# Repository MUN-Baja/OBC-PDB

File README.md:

# OBC-PDB
PCB design of Power Distribution Board and the On Board Computer with a ATMEGA2560 uC.

<ul>
  <li> Add 0 Ohm resistor dividers at all A-in to allow for configure voltage dividers
</ul>

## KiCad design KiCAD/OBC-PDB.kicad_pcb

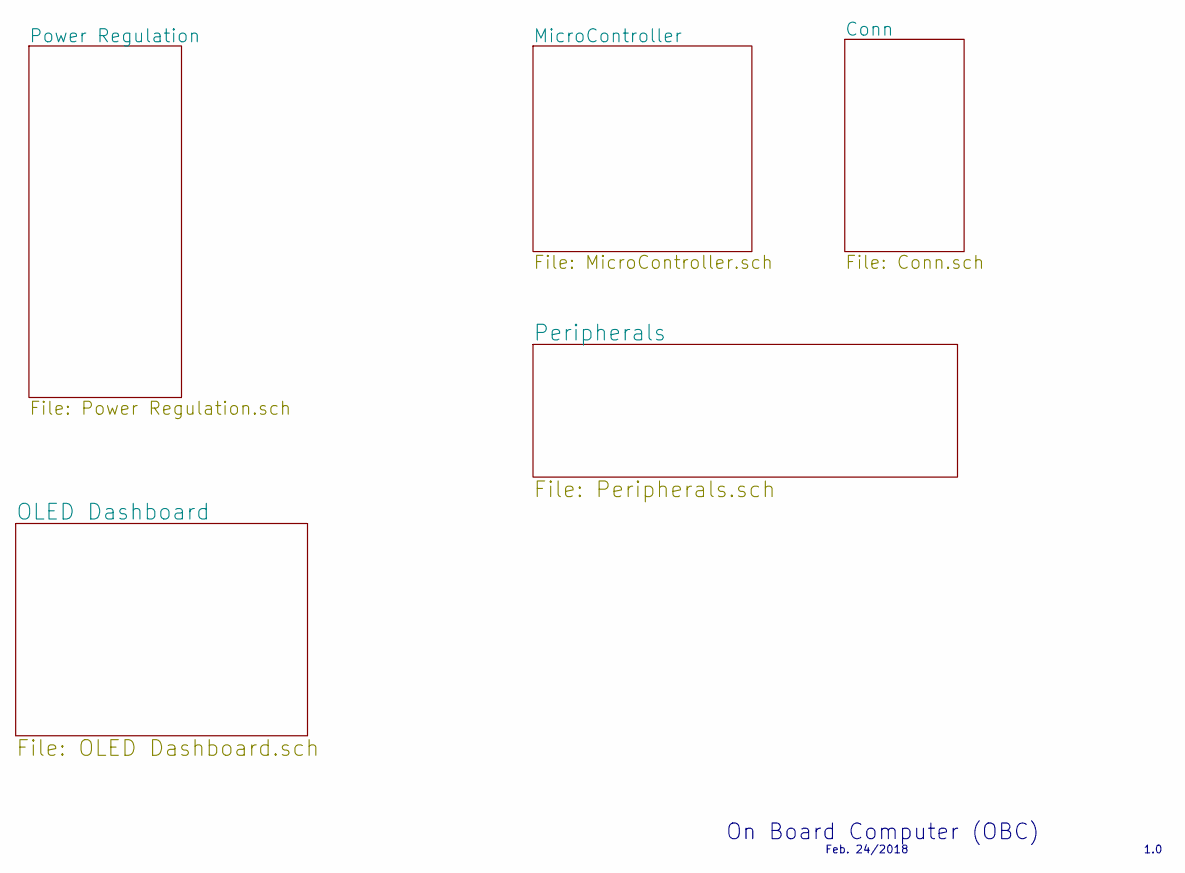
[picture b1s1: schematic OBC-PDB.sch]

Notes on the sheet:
Feb. 24/2018
On Board Computer (OBC)
1.0

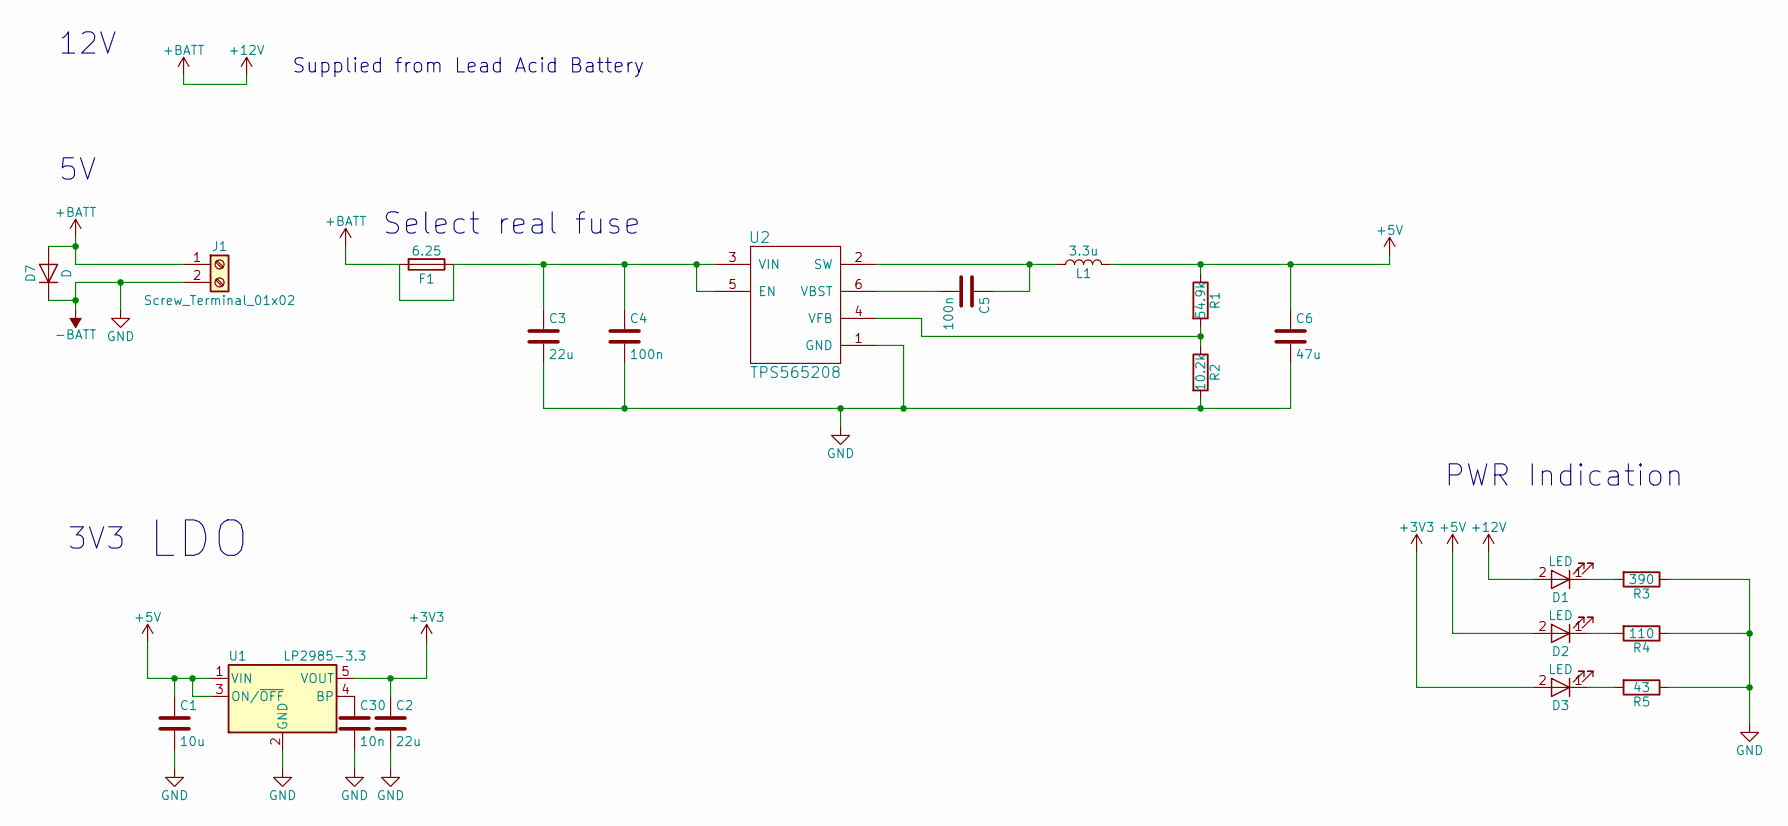
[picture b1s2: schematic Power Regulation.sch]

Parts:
C1: 10u; C_0805
C2: 22u; C_0805
C3: 22u; C_1210
C4, C5: 100n; C_0603
C6: 47u; C_1206
C30: 10n; C_0805
D1, D2, D3: LED; LED_0805
D7: D; R_Axial_DIN0204_L3.6mm_D1.6mm_P5.08mm_Horizontal
F1: 6.25
J1: Screw_Terminal_01x02; TerminalBlock_bornier-2_P5.08mm
L1: 3.3u; XAL7030
R1: 54.9k; R_0402; Tolerance 1%
R2: 10.2k; R_0402; Tolerance 1%
R3: 390; R_0805
R4: 110; R_0805
R5: 43; R_0805
U1: LP2985-3.3; SOT-23-5
U2: TPS565208; TSOT-23-6

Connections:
+3V3: C2.1, D3.2 (A), U1.5 (VOUT); also elsewhere on the board
+5V: C1.1, C6.1, D2.2 (A), L1.2, R1.1, U1.1 (VIN), U1.3 (ON/~OFF~); also elsewhere on the board
+12V: C3.1, C4.1, D1.2 (A), D7.2 (A), F1.1, F1.2, J1.1, U2.3 (VIN), U2.5 (EN); also elsewhere on the board
-BATT: C1.2, C2.2, C3.2, C4.2, C6.2, C30.2, D7.1 (K), J1.2, R2.2, R3.1, R4.1, R5.1, U1.2 (GND), U2.1 (GND); also elsewhere on the board
unnamed: C5.1, L1.1, U2.2 (SW)
unnamed: C5.2, U2.6 (VBST)
unnamed: C30.1, U1.4 (BP)
unnamed: D1.1 (K), R3.2
unnamed: D2.1 (K), R4.2
unnamed: D3.1 (K), R5.2
unnamed: R1.2, R2.1, U2.4 (VFB)

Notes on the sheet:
LDO
Select real fuse
PWR Indication
12V
Supplied from Lead Acid Battery
3V3

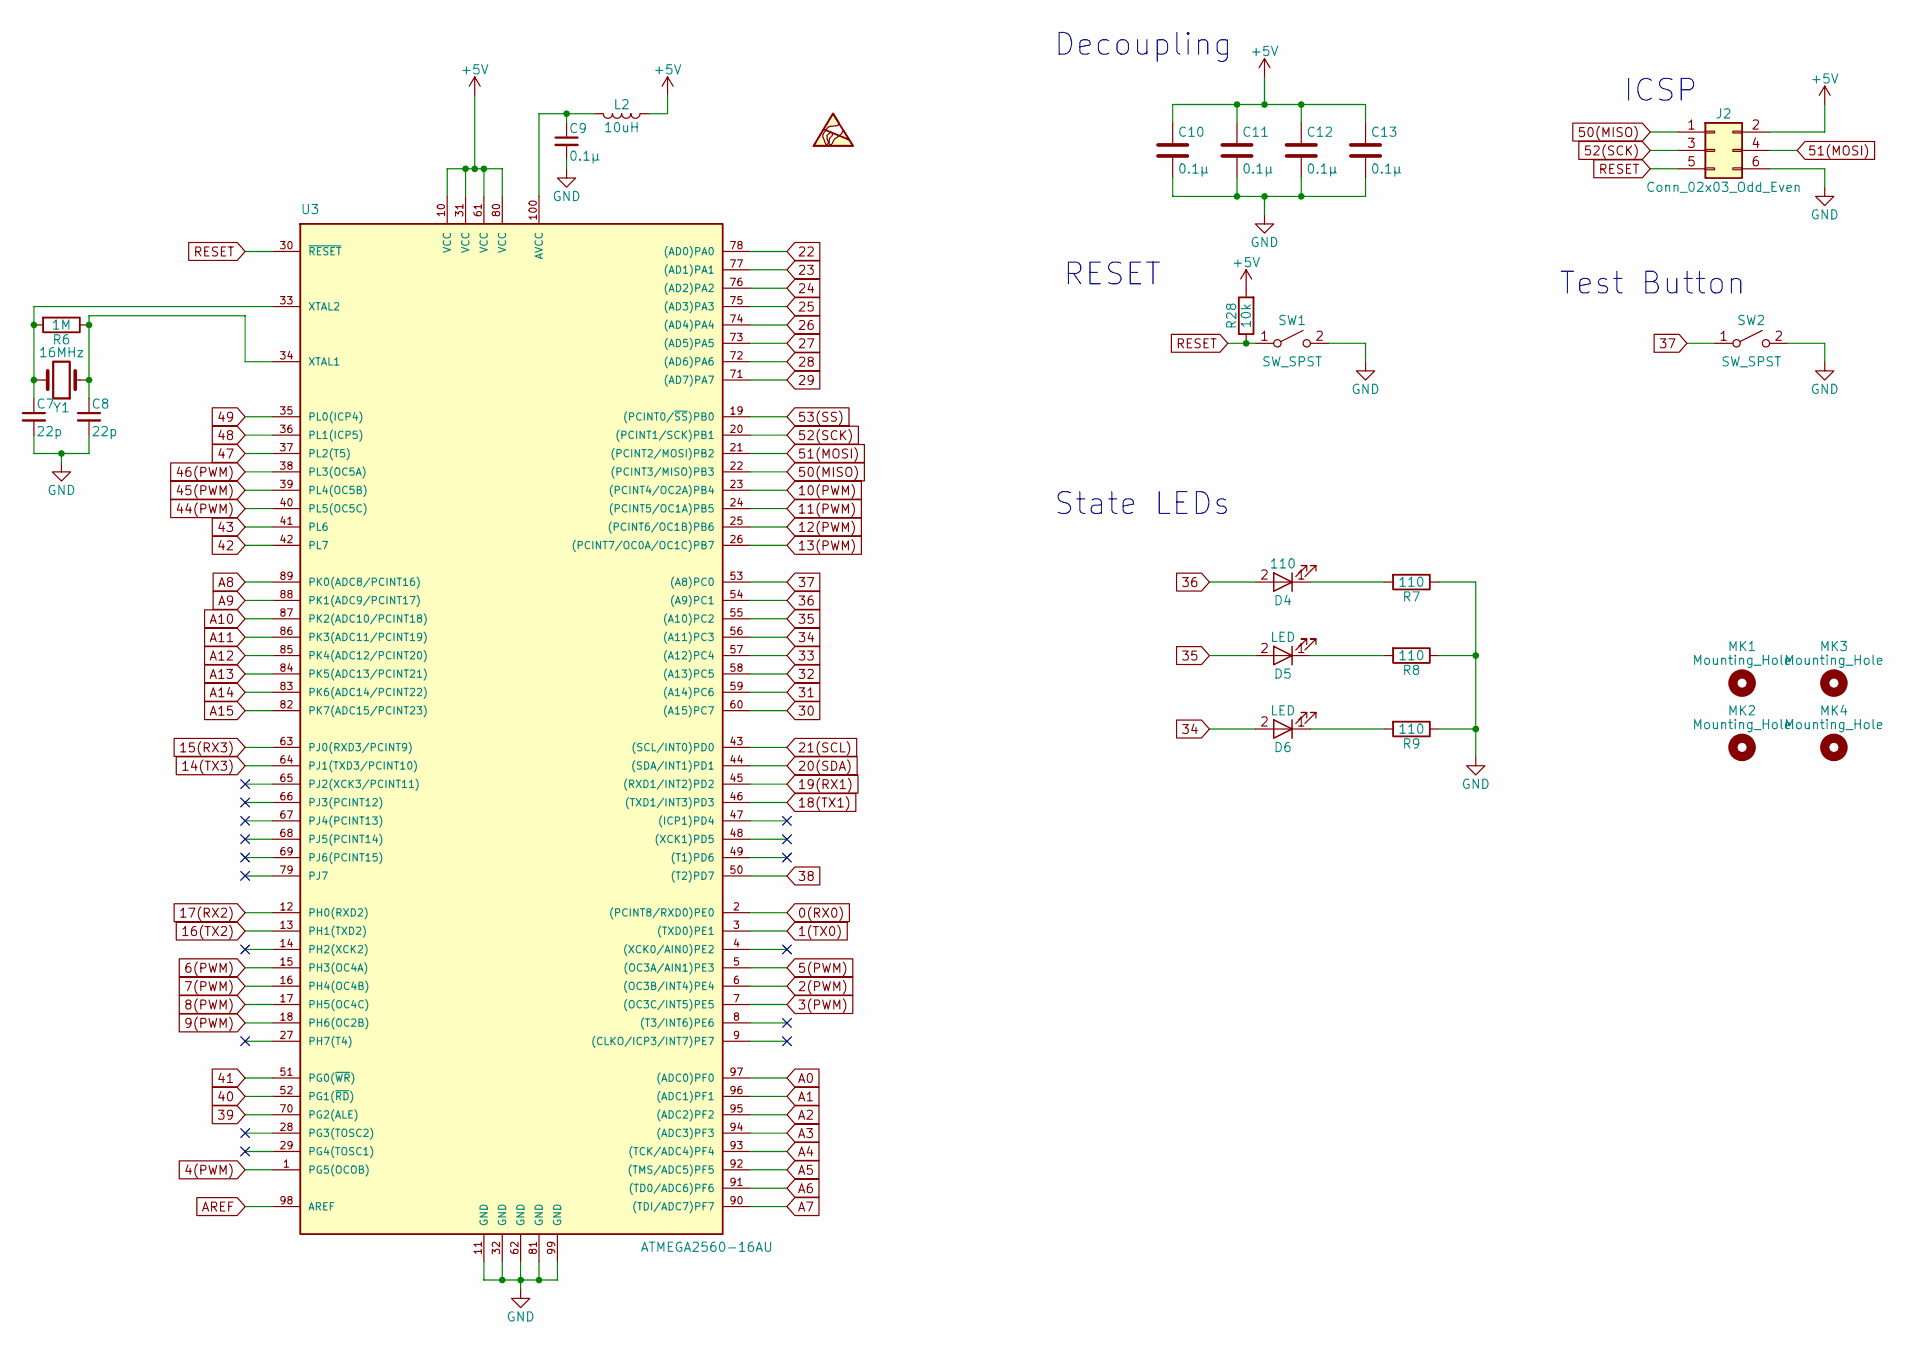
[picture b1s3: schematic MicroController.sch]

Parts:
C7, C8: 22p; C_0805
C9, C10, C11, C12, C13: 0.1µ; C_0805
D4: 110; LED_0805
D5, D6: LED; LED_0805
J2: Conn_02x03_Odd_Even; Pin_Header_Straight_2x03_Pitch2.54mm
L2: 10uH; L-1008
MK1, MK2, MK3, MK4: Mounting_Hole; MountingHole_3.2mm_M3
R6: 1M; R_0805
R7, R8, R9: 110; R_0805
R28: 10k; R_0805
SW1, SW2: SW_SPST; SW_SPST_B3U-1000P
U3: ATMEGA2560-16AU; TQFP-100_14x14mm_Pitch0.5mm
Y1: 16MHz; Crystal_HC49-U_Vertical

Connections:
5(PWM): U3.5 ((OC3A/AIN1)PE3); also elsewhere on the board
6(PWM): U3.15 (PH3(OC4A)); also elsewhere on the board
7(PWM): U3.16 (PH4(OC4B))
8(PWM): U3.17 (PH5(OC4C))
9(PWM): U3.18 (PH6(OC2B))
10(PWM): U3.23 ((PCINT4/OC2A)PB4)
11(PWM): U3.24 ((PCINT5/OC1A)PB5)
12(PWM): U3.25 ((PCINT6/OC1B)PB6); also elsewhere on the board
13(PWM): U3.26 ((PCINT7/OC0A/OC1C)PB7); also elsewhere on the board
14(TX3): U3.64 (PJ1(TXD3/PCINT10))
15(RX3): U3.63 (PJ0(RXD3/PCINT9))
16(TX2): U3.13 (PH1(TXD2)); also elsewhere on the board
17(RX2): U3.12 (PH0(RXD2)); also elsewhere on the board
18(TX1): U3.46 ((TXD1/INT3)PD3)
19(RX1): U3.45 ((RXD1/INT2)PD2)
20(SDA): U3.44 ((SDA/INT1)PD1); also elsewhere on the board
21(SCL): U3.43 ((SCL/INT0)PD0); also elsewhere on the board
22: U3.78 ((AD0)PA0); also elsewhere on the board
23: U3.77 ((AD1)PA1); also elsewhere on the board
24: U3.76 ((AD2)PA2); also elsewhere on the board
25: U3.75 ((AD3)PA3); also elsewhere on the board
26: U3.74 ((AD4)PA4); also elsewhere on the board
27: U3.73 ((AD5)PA5); also elsewhere on the board
28: U3.72 ((AD6)PA6); also elsewhere on the board
29: U3.71 ((AD7)PA7); also elsewhere on the board
30: U3.60 ((A15)PC7)
31: U3.59 ((A14)PC6); also elsewhere on the board
32: U3.58 ((A13)PC5); also elsewhere on the board
33: U3.57 ((A12)PC4); also elsewhere on the board
34: D6.2 (A), U3.56 ((A11)PC3)
35: D5.2 (A), U3.55 ((A10)PC2)
36: D4.2 (A), U3.54 ((A9)PC1)
37: SW2.1 (A), U3.53 ((A8)PC0)
38: U3.50 ((T2)PD7); also elsewhere on the board
39: U3.70 (PG2(ALE)); also elsewhere on the board
40: U3.52 (PG1(~RD~)); also elsewhere on the board
41: U3.51 (PG0(~WR~)); also elsewhere on the board
42: U3.42 (PL7); also elsewhere on the board
43: U3.41 (PL6); also elsewhere on the board
44(PWM): U3.40 (PL5(OC5C)); also elsewhere on the board
45(PWM): U3.39 (PL4(OC5B)); also elsewhere on the board
46(PWM): U3.38 (PL3(OC5A))
47: U3.37 (PL2(T5))
48: U3.36 (PL1(ICP5))
49: U3.35 (PL0(ICP4))
50(MISO): J2.1, U3.22 ((PCINT3/MISO)PB3); also elsewhere on the board
51(MOSI): J2.4, U3.21 ((PCINT2/MOSI)PB2); also elsewhere on the board
52(SCK): J2.3, U3.20 ((PCINT1/SCK)PB1); also elsewhere on the board
53(SS): U3.19 ((PCINT0/~SS~)PB0)
+5V: C10.1, C11.1, C12.1, C13.1, J2.2, L2.1, R28.2, U3.10 (VCC), U3.31 (VCC), U3.61 (VCC), U3.80 (VCC); also elsewhere on the board
-BATT: C7.2, C8.2, C9.2, C10.2, C11.2, C12.2, C13.2, J2.6, R7.1, R8.1, R9.1, SW1.2 (B), SW2.2 (B), U3.11 (GND), U3.32 (GND), U3.62 (GND), U3.81 (GND), U3.99 (GND); also elsewhere on the board
A1: U3.96 ((ADC1)PF1)
A2: U3.95 ((ADC2)PF2)
A3: U3.94 ((ADC3)PF3)
A4: U3.93 ((TCK/ADC4)PF4)
A5: U3.92 ((TMS/ADC5)PF5)
A6: U3.91 ((TD0/ADC6)PF6)
A7: U3.90 ((TDI/ADC7)PF7)
A8: U3.89 (PK0(ADC8/PCINT16)); also elsewhere on the board
A9: U3.88 (PK1(ADC9/PCINT17)); also elsewhere on the board
A10: U3.87 (PK2(ADC10/PCINT18)); also elsewhere on the board
A11: U3.86 (PK3(ADC11/PCINT19)); also elsewhere on the board
A12: U3.85 (PK4(ADC12/PCINT20)); also elsewhere on the board
A13: U3.84 (PK5(ADC13/PCINT21)); also elsewhere on the board
A14: U3.83 (PK6(ADC14/PCINT22)); also elsewhere on the board
A15: U3.82 (PK7(ADC15/PCINT23)); also elsewhere on the board
AREF: U3.98 (AREF)
unnamed: C7.1, R6.2, U3.33 (XTAL2), Y1.2
unnamed: C8.1, R6.1, U3.34 (XTAL1), Y1.1
unnamed: C9.1, L2.2, U3.100 (AVCC)
unnamed: D4.1 (K), R7.2
unnamed: D5.1 (K), R8.2
unnamed: D6.1 (K), R9.2
RESET: J2.5, R28.1, SW1.1 (A), U3.30 (~RESET)

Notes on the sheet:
Decoupling
RESET
ICSP
Test Button
State LEDs

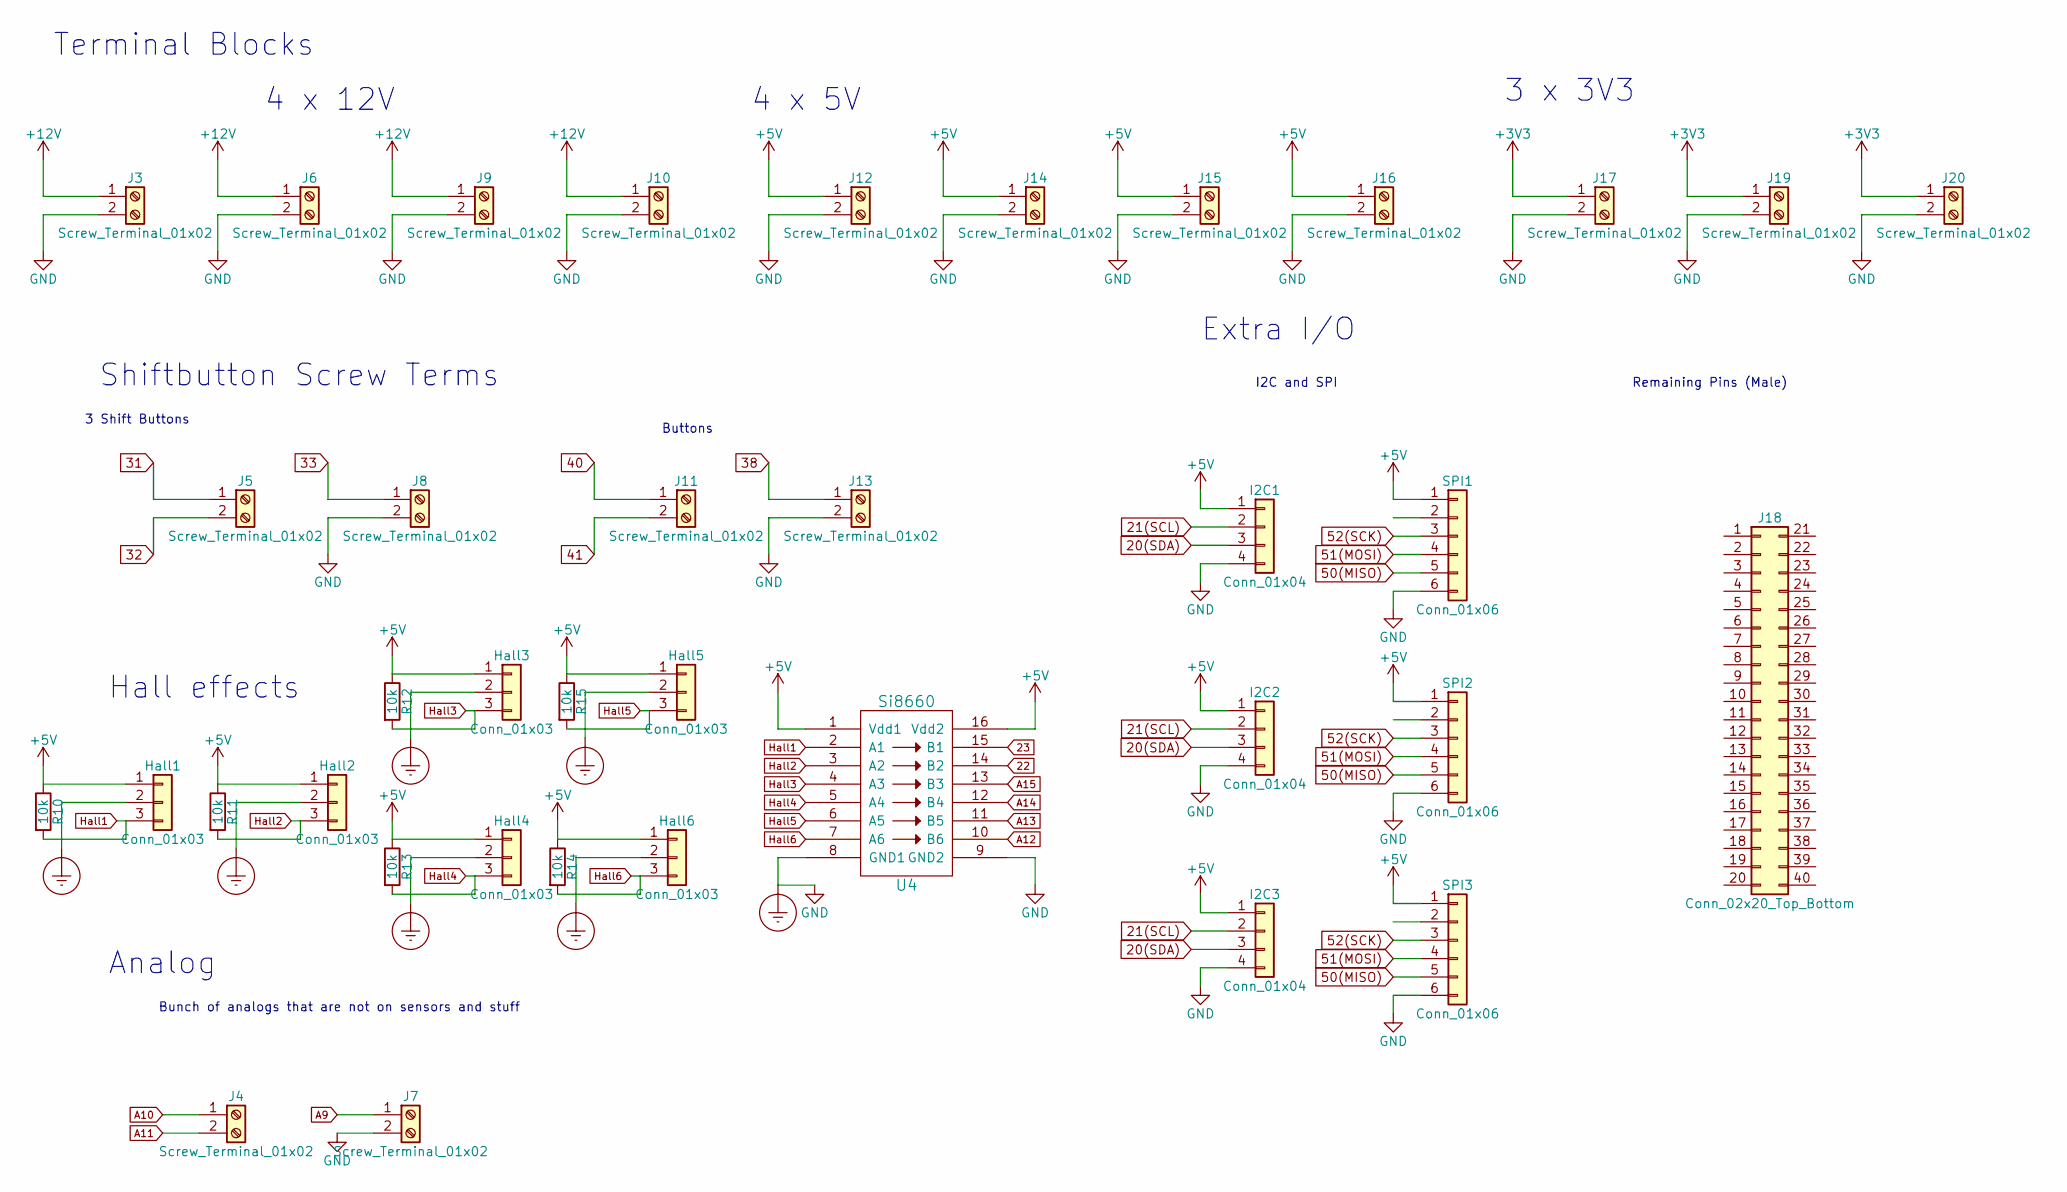
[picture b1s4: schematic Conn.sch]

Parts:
Hall1, Hall2, Hall3, Hall4, Hall5, Hall6: Conn_01x03; JST_XH_B03B-XH-A_03x2.50mm_Straight
I2C1, I2C2, I2C3: Conn_01x04; Pin_Header_Straight_1x04_Pitch2.54mm
J3, J4, J5, J6, J7, J8, J9, J10, J11, J12, J13, J14, J15, J16, J17, J19, J20: Screw_Terminal_01x02; TerminalBlock_bornier-2_P5.08mm
J18: Conn_02x20_Top_Bottom; Pin_Header_Straight_2x20_Pitch2.54mm
R10, R11, R12, R13, R14, R15: 10k; R_0805
SPI1, SPI2, SPI3: Conn_01x06; Pin_Header_Straight_1x06_Pitch2.54mm
U4: Si8660; SOIC-16W_5.3x10.2mm_Pitch1.27mm

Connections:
20(SDA): I2C1.3, I2C2.3, I2C3.3; also elsewhere on the board
21(SCL): I2C1.2, I2C2.2, I2C3.2; also elsewhere on the board
22: U4.14 (B2); also elsewhere on the board
23: U4.15 (B1); also elsewhere on the board
31: J5.1; also elsewhere on the board
32: J5.2; also elsewhere on the board
33: J8.1; also elsewhere on the board
38: J13.1; also elsewhere on the board
40: J11.1; also elsewhere on the board
41: J11.2; also elsewhere on the board
50(MISO): SPI1.5, SPI2.5, SPI3.5; also elsewhere on the board
51(MOSI): SPI1.4, SPI2.4, SPI3.4; also elsewhere on the board
52(SCK): SPI1.3, SPI2.3, SPI3.3; also elsewhere on the board
+3V3: J17.1, J19.1, J20.1; also elsewhere on the board
+5V: Hall1.1, Hall2.1, Hall3.1, Hall4.1, Hall5.1, Hall6.1, I2C1.1, I2C2.1, I2C3.1, J12.1, J14.1, J15.1, J16.1, R10.1, R11.1, R12.1, R13.1, R14.1, R15.1, SPI1.1, SPI2.1, SPI3.1, U4.1 (Vdd1), U4.16 (Vdd2); also elsewhere on the board
+12V: J3.1, J6.1, J9.1, J10.1; also elsewhere on the board
-BATT: Hall1.2, Hall2.2, Hall3.2, Hall4.2, Hall5.2, Hall6.2, I2C1.4, I2C2.4, I2C3.4, J3.2, J6.2, J7.2, J8.2, J9.2, J10.2, J12.2, J13.2, J14.2, J15.2, J16.2, J17.2, J19.2, J20.2, SPI1.6, SPI2.6, SPI3.6, U4.8 (GND1), U4.9 (GND2); also elsewhere on the board
A9: J7.1; also elsewhere on the board
A10: J4.1; also elsewhere on the board
A11: J4.2; also elsewhere on the board
A12: U4.10 (B6); also elsewhere on the board
A13: U4.11 (B5); also elsewhere on the board
A14: U4.12 (B4); also elsewhere on the board
A15: U4.13 (B3); also elsewhere on the board
Hall1: Hall1.3, R10.2, U4.2 (A1)
Hall2: Hall2.3, R11.2, U4.3 (A2)
Hall3: Hall3.3, R12.2, U4.4 (A3)
Hall4: Hall4.3, R13.2, U4.5 (A4)
Hall5: Hall5.3, R15.2, U4.6 (A5)
Hall6: Hall6.3, R14.2, U4.7 (A6)

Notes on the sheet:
Hall effects
Shiftbutton Screw Terms
Terminal Blocks
4 x 12V
4 x 5V
3 x 3V3
3 Shift Buttons
Remaining Pins (Male)
Analog
Bunch of analogs that are not on sensors and stuff
I2C and SPI
Extra I/O
Buttons

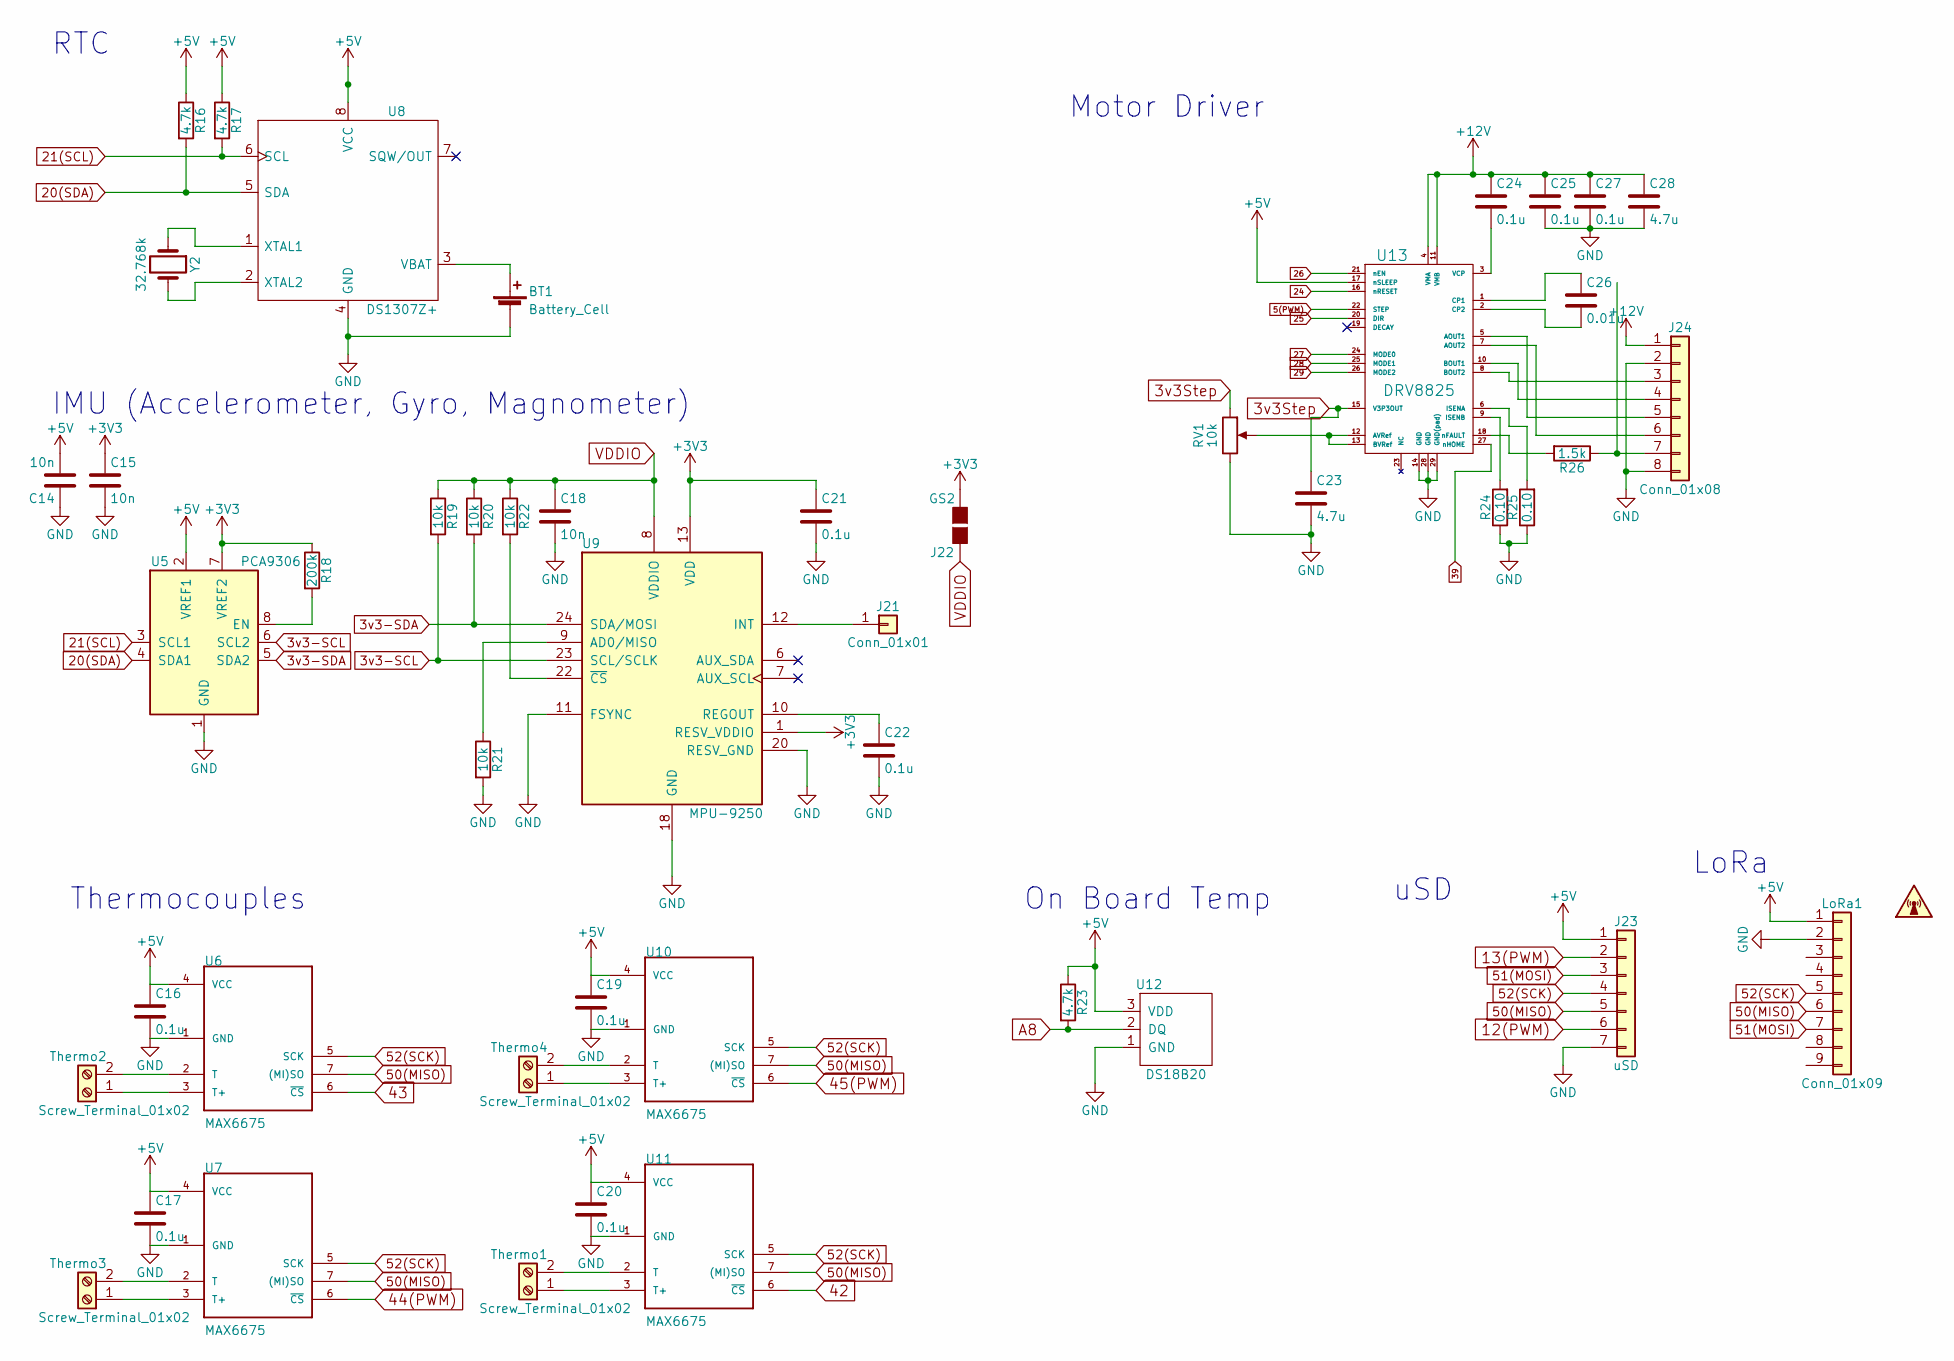
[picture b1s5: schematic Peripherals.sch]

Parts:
BT1: Battery_Cell; Keystone_1058_1x2032-CoinCell
C14, C15, C18: 10n; C_0805
C16, C17, C19, C20, C21, C22, C24, C25, C27: 0.1u; C_0805
C23, C28: 4.7u; C_0805
C26: 0.01u; C_0805
J21: Conn_01x01; Pin_Header_Straight_1x01_Pitch2.54mm
J22: GS2
J23: uSD; Pin_Header_Straight_1x07_Pitch2.54mm
J24: Conn_01x08; JST_XH_B08B-XH-A_08x2.50mm_Straight
LoRa1: Conn_01x09; Pin_Header_Straight_1x09_Pitch2.54mm
R16, R17, R23: 4.7k; R_0805
R18: 200k; R_0805
R19, R20, R21, R22: 10k; R_0805
R24, R25: 0.10; R_0805
R26: 1.5k; R_0805
RV1: 10k; Pin_Header_Straight_1x03_Pitch2.54mm
Thermo1, Thermo2, Thermo3, Thermo4: Screw_Terminal_01x02; TerminalBlock_bornier-2_P5.08mm
U5: PCA9306; VSSOP-8_2.3x2mm_Pitch0.5mm
U6, U7, U10, U11: MAX6675; SOIC-8_3.9x4.9mm_Pitch1.27mm
U8: DS1307Z+; SOIC-8_3.9x4.9mm_Pitch1.27mm
U9: MPU-9250; QFN-24-1EP_3x3mm_Pitch0.4mm
U12: DS18B20; TO-92_Inline_Narrow_Oval
U13: DRV8825; HTSSOP-32_6.1x11mm_Pitch0.65mm_ThermalPad
Y2: 32.768k; Crystal_C26-LF_d2.1mm_l6.5mm_Horizontal

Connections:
3v3-SCL: R19.2, U5.6 (SCL2), U9.23 (SCL/SCLK)
3v3-SDA: R20.2, U5.5 (SDA2), U9.24 (SDA/MOSI)
3v3Step: C23.1, RV1.1, U13.15 (V3P3OUT)
5(PWM): U13.22 (STEP); also elsewhere on the board
12(PWM): J23.6; also elsewhere on the board
13(PWM): J23.2; also elsewhere on the board
20(SDA): R16.2, U5.4 (SDA1), U8.5 (SDA); also elsewhere on the board
21(SCL): R17.2, U5.3 (SCL1), U8.6 (SCL); also elsewhere on the board
24: U13.16 (nRESET); also elsewhere on the board
25: U13.20 (DIR); also elsewhere on the board
26: U13.21 (nEN); also elsewhere on the board
27: U13.24 (MODE0); also elsewhere on the board
28: U13.25 (MODE1); also elsewhere on the board
29: U13.26 (MODE2); also elsewhere on the board
39: U13.27 (nHOME); also elsewhere on the board
42: U11.6 (~CS~); also elsewhere on the board
43: U6.6 (~CS~); also elsewhere on the board
44(PWM): U7.6 (~CS~); also elsewhere on the board
45(PWM): U10.6 (~CS~); also elsewhere on the board
50(MISO): J23.5, LoRa1.6, U6.7 ((MI)SO), U7.7 ((MI)SO), U10.7 ((MI)SO), U11.7 ((MI)SO); also elsewhere on the board
51(MOSI): J23.3, LoRa1.7; also elsewhere on the board
52(SCK): J23.4, LoRa1.5, U6.5 (SCK), U7.5 (SCK), U10.5 (SCK), U11.5 (SCK); also elsewhere on the board
+3V3: C15.1, C21.1, J22.2 (G2), R18.1, U5.7 (VREF2), U9.1 (RESV_VDDIO), U9.13 (VDD); also elsewhere on the board
+5V: C14.2, C16.1, C17.1, C19.1, C20.1, J23.1, LoRa1.1, R16.1, R17.1, R23.1, U5.2 (VREF1), U6.4 (VCC), U7.4 (VCC), U8.8 (VCC), U10.4 (VCC), U11.4 (VCC), U12.3 (VDD), U13.17 (nSLEEP); also elsewhere on the board
+12V: C24.1, C25.1, C27.1, C28.1, J24.1, U13.4 (VMA), U13.11 (VMB); also elsewhere on the board
-BATT: BT1.2 (-), C14.1, C15.2, C16.2, C17.2, C18.2, C19.2, C20.2, C21.2, C22.2, C23.2, C25.2, C27.2, C28.2, J23.7, J24.2, J24.8, LoRa1.2, R21.2, R24.1, R25.1, RV1.3, U5.1 (GND), U6.1 (GND), U7.1 (GND), U8.4 (GND), U9.11 (FSYNC), U9.18 (GND), U9.20 (RESV_GND), U10.1 (GND), U11.1 (GND), U12.1 (GND), U13.14 (GND), U13.28 (GND), U13.29 (GND(pad)); also elsewhere on the board
A8: R23.2, U12.2 (DQ); also elsewhere on the board
unnamed: BT1.1 (+), U8.3 (VBAT)
unnamed: C22.1, U9.10 (REGOUT)
unnamed: C24.2, U13.3 (VCP)
unnamed: C26.1, U13.1 (CP1)
unnamed: C26.2, U13.2 (CP2)
unnamed: J21.1, U9.12 (INT)
unnamed: J24.3, U13.8 (BOUT2)
unnamed: J24.4, U13.10 (BOUT1)
unnamed: J24.5, U13.5 (AOUT1)
unnamed: J24.6, U13.7 (AOUT2)
unnamed: J24.7, R26.1
unnamed: R18.2, U5.8 (EN)
unnamed: R21.1, U9.9 (AD0/MISO)
unnamed: R22.2, U9.22 (~CS)
unnamed: R24.2, U13.9 (ISENB)
unnamed: R25.2, U13.6 (ISENA)
unnamed: R26.2, U13.18 (nFAULT)
unnamed: RV1.2, U13.12 (AVRef), U13.13 (BVRef)
unnamed: Thermo1.1, U11.3 (T+)
unnamed: Thermo1.2, U11.2 (T)
unnamed: Thermo2.1, U6.3 (T+)
unnamed: Thermo2.2, U6.2 (T)
unnamed: Thermo3.1, U7.3 (T+)
unnamed: Thermo3.2, U7.2 (T)
unnamed: Thermo4.1, U10.3 (T+)
unnamed: Thermo4.2, U10.2 (T)
unnamed: U8.1 (XTAL1), Y2.1
unnamed: U8.2 (XTAL2), Y2.2
VDDIO: C18.1, J22.1 (G1), R19.1, R20.1, R22.1, U9.8 (VDDIO)

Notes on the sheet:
Motor Driver
Thermocouples
uSD
LoRa
RTC
IMU (Accelerometer, Gyro, Magnometer)
On Board Temp

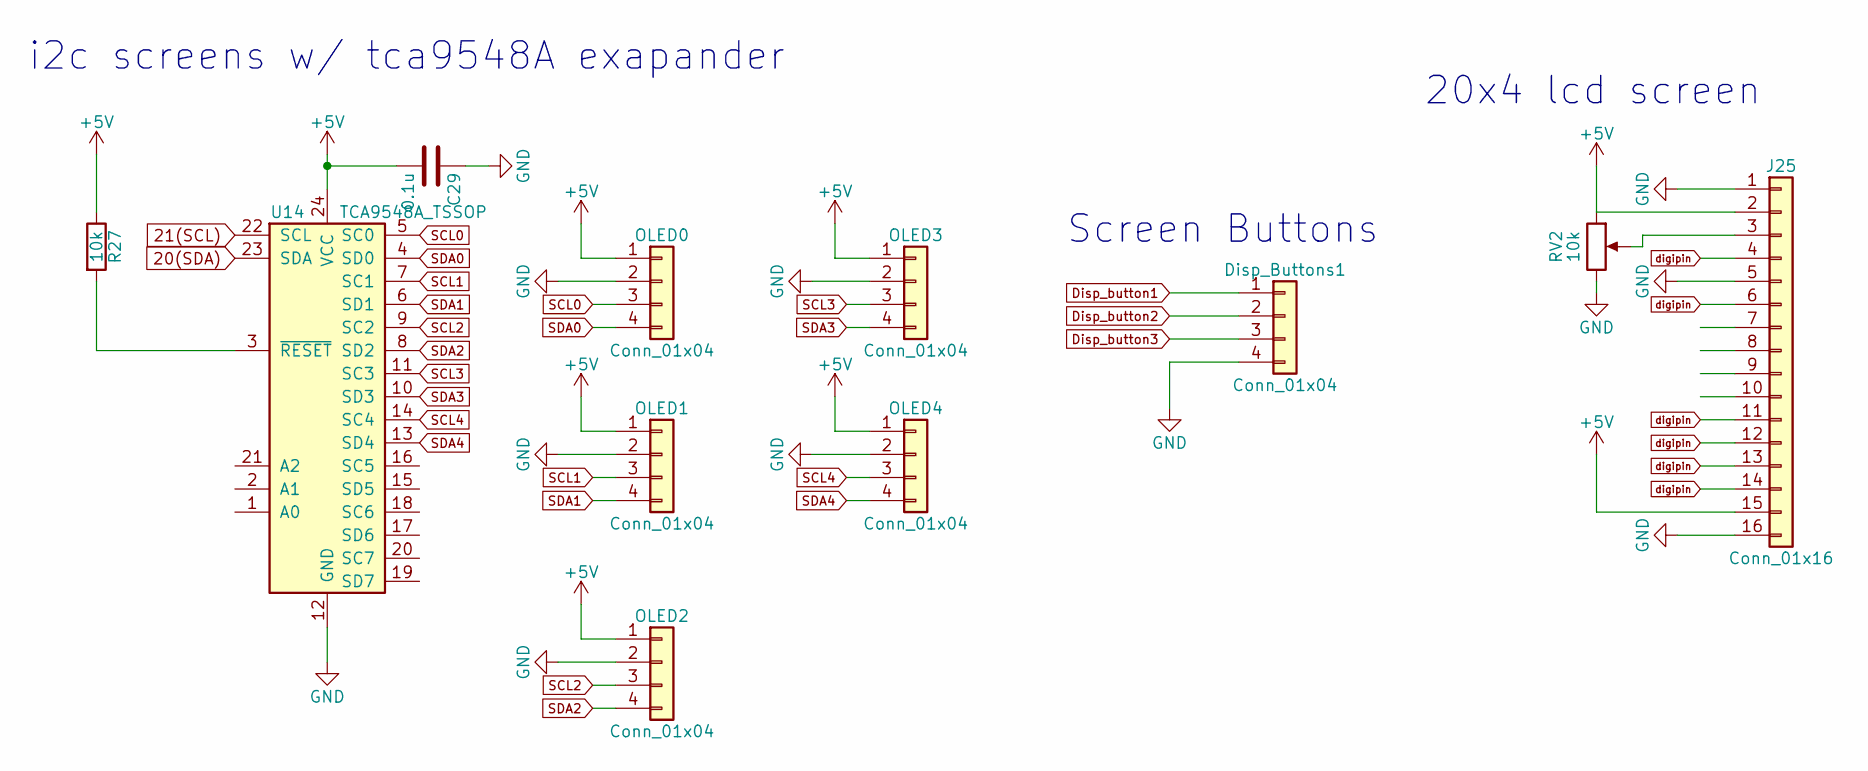
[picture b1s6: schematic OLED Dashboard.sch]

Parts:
C29: 0.1u; C_0805
Disp_Buttons1: Conn_01x04; Pin_Header_Straight_1x04_Pitch2.54mm
J25: Conn_01x16; Pin_Header_Straight_1x16_Pitch2.54mm
OLED0, OLED1, OLED2, OLED3, OLED4: Conn_01x04; Pin_Header_Straight_1x04_Pitch2.54mm
R27: 10k; R_0805
RV2: 10k; Pin_Header_Straight_1x03_Pitch2.54mm
U14: TCA9548A_TSSOP; TSSOP-24_4.4x7.8mm_Pitch0.65mm

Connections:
6(PWM): U14.21 (A2); also elsewhere on the board
16(TX2): U14.2 (A1); also elsewhere on the board
17(RX2): U14.1 (A0); also elsewhere on the board
20(SDA): U14.23 (SDA); also elsewhere on the board
21(SCL): U14.22 (SCL); also elsewhere on the board
+5V: C29.2, J25.2, J25.15, OLED0.1, OLED1.1, OLED2.1, OLED3.1, OLED4.1, R27.1, RV2.1, U14.24 (VCC); also elsewhere on the board
-BATT: C29.1, Disp_Buttons1.4, J25.1, J25.5, J25.16, OLED0.2, OLED1.2, OLED2.2, OLED3.2, OLED4.2, RV2.3, U14.12 (GND); also elsewhere on the board
Disp_button1: Disp_Buttons1.1
Disp_button2: Disp_Buttons1.2
Disp_button3: Disp_Buttons1.3
unnamed: J25.3, RV2.2
unnamed: R27.2, U14.3 (~RESET)
SCL0: OLED0.3, U14.5 (SC0)
SCL1: OLED1.3, U14.7 (SC1)
SCL2: OLED2.3, U14.9 (SC2)
SCL3: OLED3.3, U14.11 (SC3)
SCL4: OLED4.3, U14.14 (SC4)
SDA0: OLED0.4, U14.4 (SD0)
SDA1: OLED1.4, U14.6 (SD1)
SDA2: OLED2.4, U14.8 (SD2)
SDA3: OLED3.4, U14.10 (SD3)
SDA4: OLED4.4, U14.13 (SD4)

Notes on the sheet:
i2c screens w/ tca9548A exapander
20x4 lcd screen
Screen Buttons

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
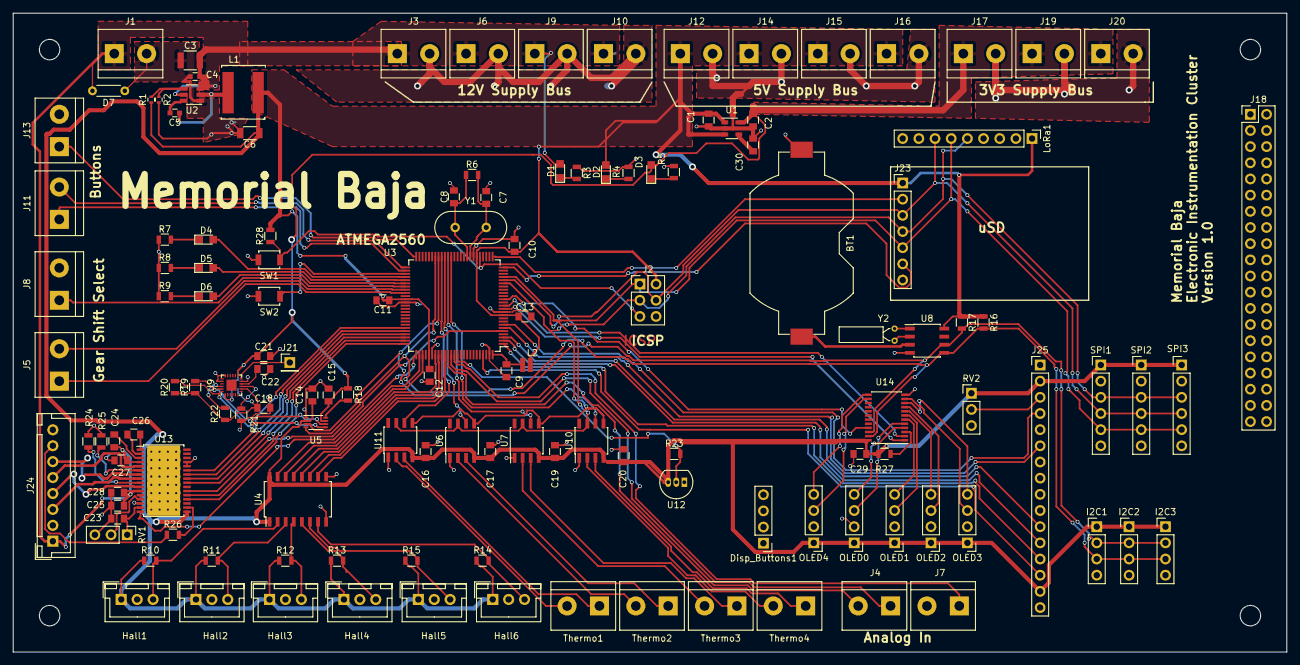
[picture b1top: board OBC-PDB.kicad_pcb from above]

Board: 2 copper layers, 200.0 x 100.3 mm, 140 parts (1 on the bottom side), 116 nets.

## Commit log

2018-02-09 init and folders
2018-02-22 added board sheet arch
2018-02-24 completed 5V buck schematic and setup
2018-02-25 added MC but N/C
2018-03-08 µC ATMEGA2560 added and pins labeled, w/ supp components
2018-05-03 Schematic small fix
2018-05-05 transfer for mechanical step
2018-05-05 step file
2018-05-05 added mech package
2018-05-11 fixed diode
